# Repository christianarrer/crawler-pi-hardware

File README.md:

# crawler-pi-hardware

Hardware designs for **crawler-pi**, an autonomous tracked robot based on a Raspberry Pi and ROS 2.

This repository contains KiCad PCB projects, manufacturing files, and hardware documentation. Additional 3D-printable customization parts may be included in the future, subject to the necessary permissions.

The ROS 2 software is maintained separately in [crawler-pi](https://github.com/christianarrer/crawler-pi).

## PCB projects

### 1. crawler-pi — Sensor and power distribution board

**Location:** [`pcb/crawler-pi/`](pcb/crawler-pi/)

A distribution and interface PCB for the crawler's Raspberry Pi electronics. Its purpose is to simplify the wiring between the Raspberry Pi, sensors, motor-driver control signals, lighting, and power components.

The board provides:

- Connections for I²C sensors and related peripheral wiring.
- GPIO connections for the left and right motor-driver control signals.
- A GPIO-controlled switch for the headlights.
- Battery and DC/DC buck-converter connections for the crawler's power distribution.
- Reverse-polarity protection and fuse protection.

The project includes KiCad schematic and PCB design files. The [`gerber/`](pcb/crawler-pi/gerber/) directory contains manufacturing outputs from an earlier board revision.

#### Through-hole (THT) components — hand soldering

The following **19 components** require through-hole hand soldering. The reference designators and part numbers are reproduced from the original BOM (including `BS170` and `178.6165.0001`).

| Reference | Manufacturer | MPN | LCSC | Type |
| --- | --- | --- | --- | --- |
| R_POL_PD1 | VISHAY | RN60E1003BRE6 | C1796719 | Resistor |
| R_LED_GATE1 | YAGEO | MFR-25FRF52-100R | C1740087 | Resistor |
| R_LED_PD1 | VISHAY | RN60E1003BRE6 | C1796719 | Resistor |
| Q_PMOS_GDS | onsemi | FQP27P06 | C462764 | p-channel MOSFET |
| BS170 | onsemi | BS170 | C111691 | n-channel MOSFET |
| 178.6165.0001 | Littelfuse | 178.6165.0001 | C207060 | Fuseholder |
| J_BATT1 | CUI | TB010-508-02BE | C5954901 | Terminal Block |
| J_MOT_DRV_L_PWR1 | CUI | TB010-508-02BE | C5954901 | Terminal Block |
| J_MOT_DRV_R_PWR1 | CUI | TB010-508-02BE | C5954901 | Terminal Block |
| J_PWR_SWITCH1 | CUI | TB010-508-02BE | C5954901 | Terminal Block |
| J_POWER_MON_PWR1 | Amphenol | VI0421550000G | C3816565 | Terminal Block |
| J_BUCk1 | Amphenol | VI0421550000G | C3816565 | Terminal Block |
| J_RPI1 | ZHOURI | PC104-2*20 | C5307344 | Pin Stacking Header 2x20 |
| J_PWR_MON_I2C1 | hanxia | HX PH254-01-04-Z-L11.5 | C52016392 | Pin Header 1x4 |
| J_ODO_L_I2C1 | hanxia | HX PH254-01-04-Z-L11.5 | C52016392 | Pin Header 1x4 |
| J_IMU_I2C1 | hanxia | HX PH254-01-04-Z-L11.5 | C52016392 | Pin Header 1x4 |
| J_ODO_R_I2C1 | hanxia | HX PH254-01-04-Z-L11.5 | C52016392 | Pin Header 1x4 |
| J_MOT_DRV_L_CTRL1 | hanxia | HX PZ2.54-2x4P ZZ | C32713277 | Pin Header 2x4 |
| J_MOT_DRV_R_CTRL1 | hanxia | HX PZ2.54-2x4P ZZ | C32713277 | Pin Header 2x4 |

**Documentation still to be added:** connector assignments, assembly instructions, and board-specific wiring notes. Consult the schematic and PCB files for authoritative pin assignments and component values.

### 2. crawler-pi-charger — NiMH charger and power-path board

**Location:** [`pcb/crawler-pi-charger/`](pcb/crawler-pi-charger/)

**Status: Work in progress — not yet validated for construction or operation.**

This project aims to provide an integrated charging and power-path solution for the crawler's **6-cell (7.2 V nominal) NiMH battery pack** and docking station.

The design is based on the **Analog Devices LTC4011** NiMH battery charger controller. The intended functionality includes:

- Charging the NiMH battery when the crawler is connected to its dock.
- Using the LTC4011's supported fast-charge termination and battery-temperature sensing features.
- Providing a power path between the external dock supply, battery, and crawler system load.
- Supporting continued system operation when docking power is connected or removed, subject to the final switching and power-budget design.
- Interfaces for the docking-station supply, battery, system power, and DC/DC converter connections.

The design explores MOSFET-based power-path switching inspired by the Analog Devices DC674B demonstration circuit. Power-path component ratings, charger configuration, thermal protection, current limits, and the distribution of power to the motors and Raspberry Pi must be verified before use.

**Important:** This is an experimental hardware project. Do not assume that the present schematic is suitable for unattended battery charging or direct connection to the robot without electrical verification and testing.

## Repository structure

```text
crawler-pi-hardware/
├── pcb/
│   ├── crawler-pi/          # Sensor, GPIO, and power distribution PCB
│   │   └── gerber/          # Manufacturing files
│   └── crawler-pi-charger/  # NiMH charger and power-path PCB (WIP)
└── stl/                     # Possible future 3D-printable parts
```

The `stl/` directory is **planned**, not necessarily present in the repository. Original designs or adaptations of third-party parts will only be published where redistribution is permitted.

## Working with the designs

Open each PCB project using its `.kicad_pro` file in KiCad. Before ordering or assembling boards, review the schematic, PCB layout, design-rule checks, component footprints, and manufacturing outputs. Existing Gerber files represent a particular exported revision and should not be assumed to match subsequent schematic or PCB edits.

## License

See [LICENSE](LICENSE) for the repository's current license. Rights to any third-party reference designs, components, and future mechanical files remain subject to their respective owners and licenses.

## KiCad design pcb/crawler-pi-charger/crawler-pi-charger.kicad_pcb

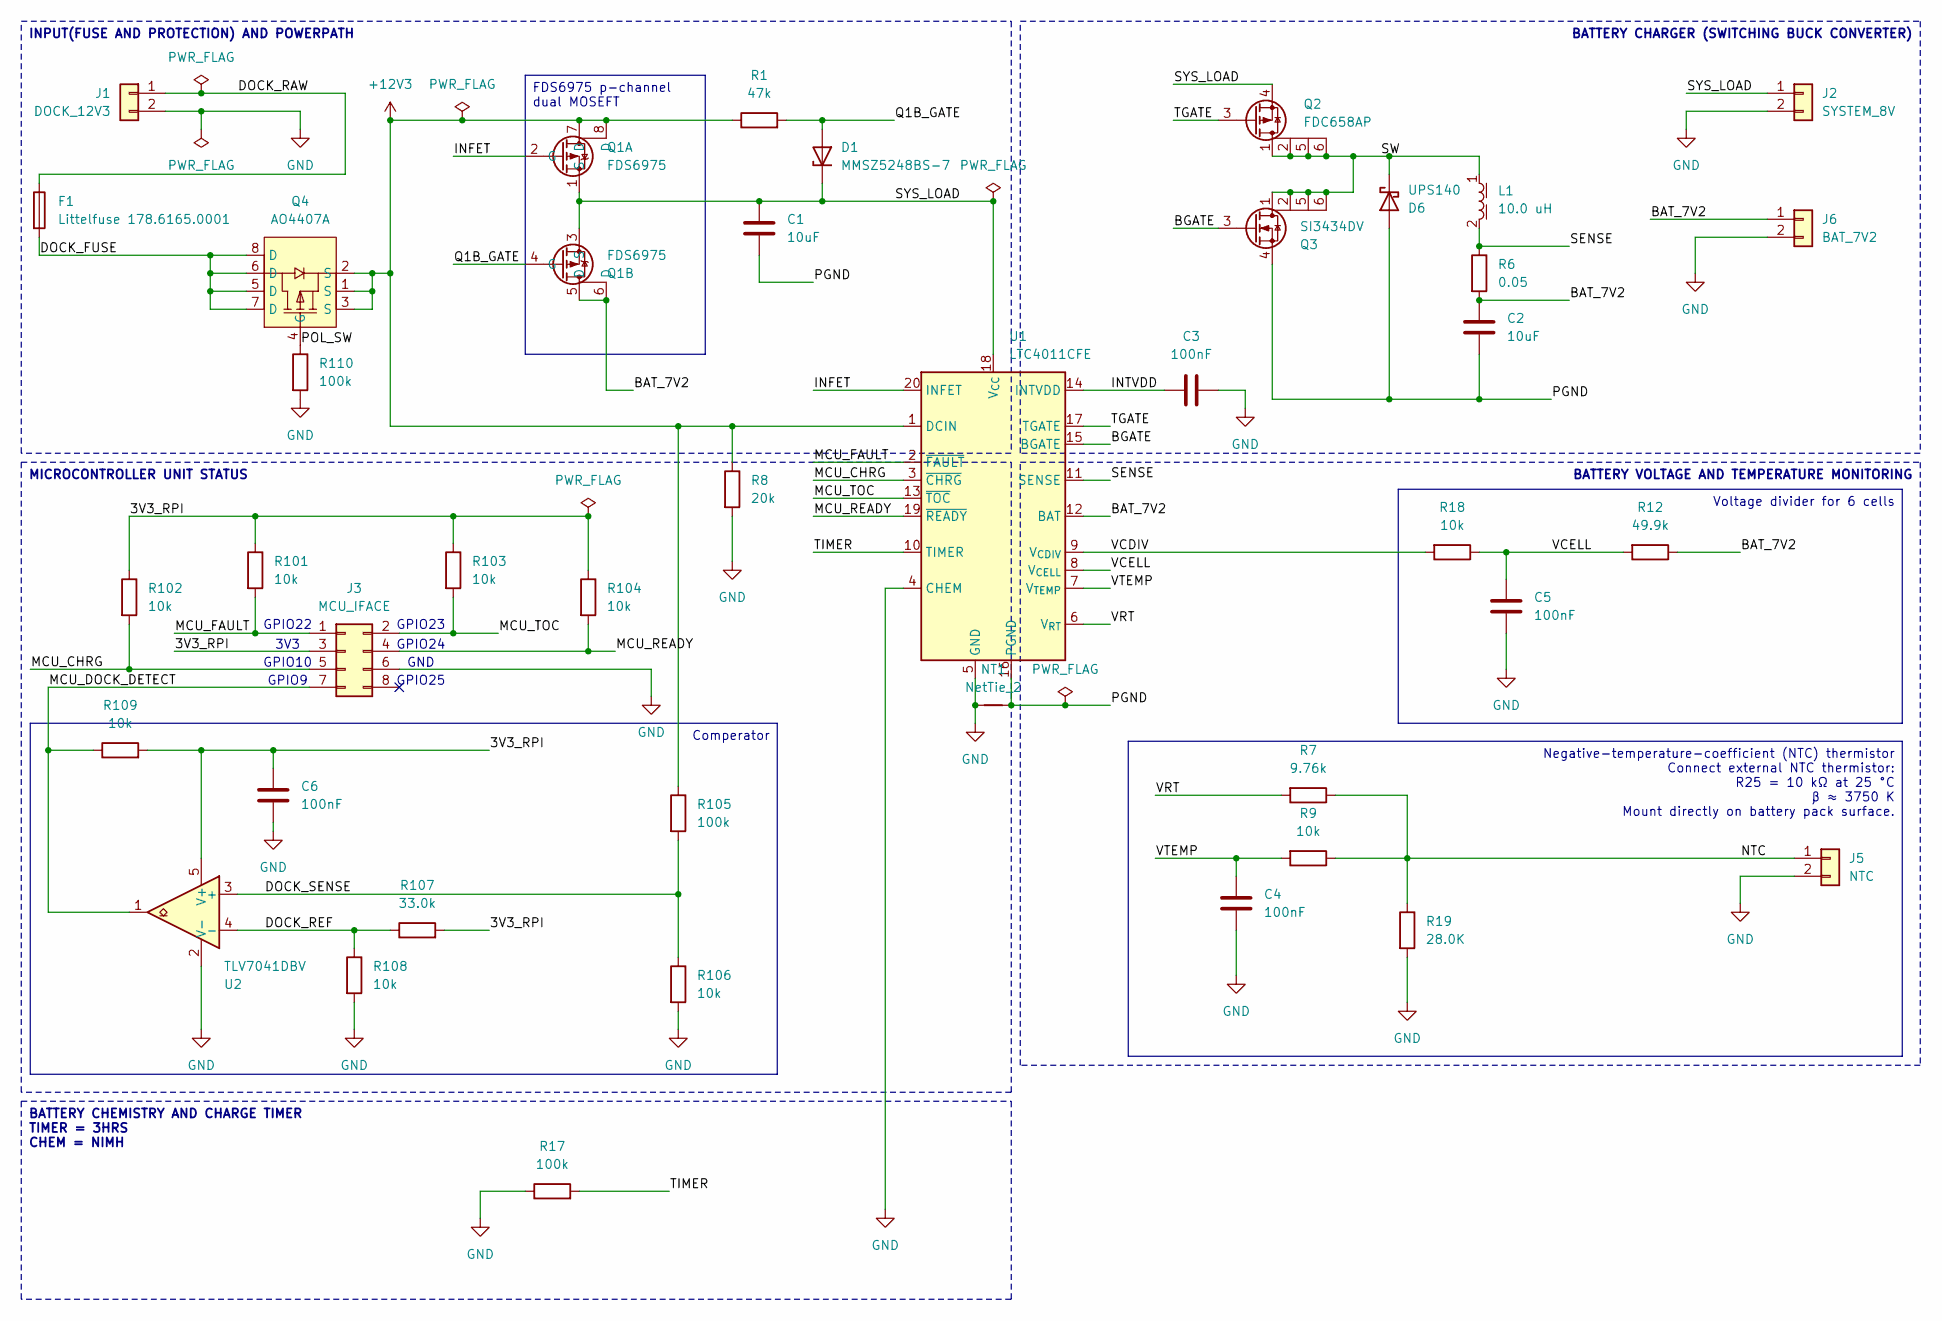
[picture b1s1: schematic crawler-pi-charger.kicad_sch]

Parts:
C1, C2: 10uF; C_1210_3225Metric; MPN TMK325BJ106MM-T; LCSC C92835
C3, C4, C5: 100nF; C_0603_1608Metric; MPN 06033D104KAT2A; LCSC C179462
C6: 100nF; C_0603_1608Metric; MPN CC0603KRX7R9BB104; LCSC C14663
D1: MMSZ5248BS-7; D_SOD-323; MPN MMSZ5248BS-7; LCSC C460919
D6: UPS140; D_Powermite_LargeCathode; MPN UPS140E3/TR7; LCSC C3757274
F1: Littelfuse 178.6165.0001; FuseHolder_Blade_ATO_Littelfuse_FLR_178.6165; MPN 178.6165.0001; LCSC C207060
J1: DOCK_12V3; TerminalBlock_CUI_TB007-508-02_1x02_P5.08mm_Horizontal
J2: SYSTEM_8V; TerminalBlock_CUI_TB007-508-02_1x02_P5.08mm_Horizontal
J3: MCU_IFACE; PinHeader_2x04_P2.54mm_Vertical
J5: NTC; TerminalBlock_CUI_TB007-508-02_1x02_P5.08mm_Horizontal
J6: BAT_7V2; TerminalBlock_CUI_TB007-508-02_1x02_P5.08mm_Horizontal
L1: 10.0 uH; L_Wurth_WE-LHMI-7050; Part Number 74437349100
NT1: NetTie_2; NetTie-2_SMD_Pad0.5mm
Q1: FDS6975; SOIC-8_3.9x4.9mm_P1.27mm; MPN FDS6975; LCSC C903635
Q2: FDC658AP; SuperSOT-6; MPN FDC658AP; LCSC C3280198
Q3: SI3434DV; TSOP-6_1.65x3.05mm_P0.95mm; MPN SI3434DV-T1-E3; LCSC C5456592
Q4: AO4407A; SOIC-8_3.9x4.9mm_P1.27mm; MPN AO4407A; LCSC C16072
R1: 47k; R_0402_1005Metric; MPN CRCW040247K0JNED; LCSC C71619
R6: 0.05; R_1206_3216Metric; MPN ERJ-L08KJ50MV; LCSC C3914720
R7: 9.76k; R_0402_1005Metric; MPN CRCW04029K76FKED; LCSC C843909
R8: 20k; R_0402_1005Metric; MPN CRCW040220K0JNED; LCSC C482264
R9, R18, R101, R102, R103, R104, R106, R108, R109: 10k; R_0402_1005Metric; MPN CRCW040210K0FKED; LCSC C71617
R12: 49.9k; R_0402_1005Metric; MPN CRCW040249K9FKED; LCSC C350874
R17, R105, R110: 100k; R_0402_1005Metric; MPN CRCW0402100KFKED; LCSC C481918
R19: 28.0K; R_0402_1005Metric; MPN CRCW040228K0FKED; LCSC C844308
R107: 33.0k; R_0402_1005Metric; MPN CRCW040233K0FKED; LCSC C482153
U1: LTC4011CFE; HTSSOP-20-1EP_4.4x6.5mm_P0.65mm_EP2.74x3.86mm; MPN LTC4011CFE#TRPBF; LCSC C580822
U2: TLV7041DBV; SOT-23-5; MPN TLV7041DBVR; LCSC C702122

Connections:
+12V3: Q1.7 (D), Q1.8 (D), Q4.1 (S), Q4.2 (S), Q4.3 (S), R1.1, R8.1, R105.1, U1.1 (DCIN)
/3V3_RPI: C6.1, J3.3, R101.1, R102.1, R103.1, R104.1, R107.2, R109.2, U2.5 (V+)
/BAT_7V2: C2.1, J6.1, Q1.5 (D), Q1.6 (D), R6.2, R12.1, U1.12 (BAT)
/BGATE: Q3.3 (G), U1.15 (BGATE)
/DOCK_FUSE: F1.2, Q4.5 (D), Q4.6 (D), Q4.7 (D), Q4.8 (D)
/DOCK_RAW: F1.1, J1.1
/DOCK_REF: R107.1, R108.1, U2.4 (-)
/DOCK_SENSE: R105.2, R106.1, U2.3 (+)
/INFET: Q1.2 (G), U1.20 (INFET)
/INTVDD: C3.1, U1.14 (INTVDD)
/MCU_CHRG: J3.5, R102.2, U1.3 (~CHRG)
/MCU_DOCK_DETECT: J3.7, R109.1, U2.1
/MCU_FAULT: J3.1, R101.2, U1.2 (~FAULT)
/MCU_READY: J3.4, R104.2, U1.19 (~READY)
/MCU_TOC: J3.2, R103.2, U1.13 (~TOC)
/NTC: J5.1, R7.1, R9.1, R19.1
/PGND: C1.2, C2.2, D6.2 (A), NT1.2, Q3.4 (S), U1.16 (PGND)
/POL_SW: Q4.4 (G), R110.1
/Q1B_GATE: D1.2 (A), Q1.4 (G), R1.2
/SENSE: L1.2, R6.1, U1.11 (SENSE)
/SW: D6.1 (K), L1.1, Q2.1 (D), Q2.2 (D), Q2.5 (D), Q2.6 (D), Q3.1 (D), Q3.2 (D), Q3.5 (D), Q3.6 (D)
/SYS_LOAD: C1.1, D1.1 (K), J2.1, Q1.1 (S), Q1.3 (S), Q2.4 (S), U1.18 (V_{CC})
/TGATE: Q2.3 (G), U1.17 (TGATE)
/TIMER: R17.2, U1.10 (TIMER)
/VCDIV: R18.2, U1.9 (V_{CDIV})
/VCELL: C5.1, R12.2, R18.1, U1.8 (V_{CELL})
/VRT: R7.2, U1.6 (V_{RT})
/VTEMP: C4.1, R9.2, U1.7 (V_{TEMP})
GND: C3.2, C4.2, C5.2, C6.2, J1.2, J2.2, J3.6, J5.2, J6.2, NT1.1, R8.2, R17.1, R19.2, R106.2, R108.2, R110.2, U1.4 (CHEM), U1.5 (GND), U1.21 (GND), U2.2 (V-)

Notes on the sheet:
GPIO24
GPIO9
GPIO22
GND
GPIO25
GPIO10
3V3
GPIO23
Negative-temperature-coefficient (NTC) thermistor Connect external NTC thermistor: R25 = 10 kΩ at 25 °C β ≈ 3750 K Mount directly on battery pack surface.
BATTERY CHARGER (SWITCHING BUCK CONVERTER)
Comperator
BATTERY VOLTAGE AND TEMPERATURE MONITORING
BATTERY CHEMISTRY AND CHARGE TIMER TIMER = 3HRS CHEM = NIMH
INPUT(FUSE AND PROTECTION) AND POWERPATH
MICROCONTROLLER UNIT STATUS
Voltage divider for 6 cells
FDS6975 p-channel dual MOSEFT

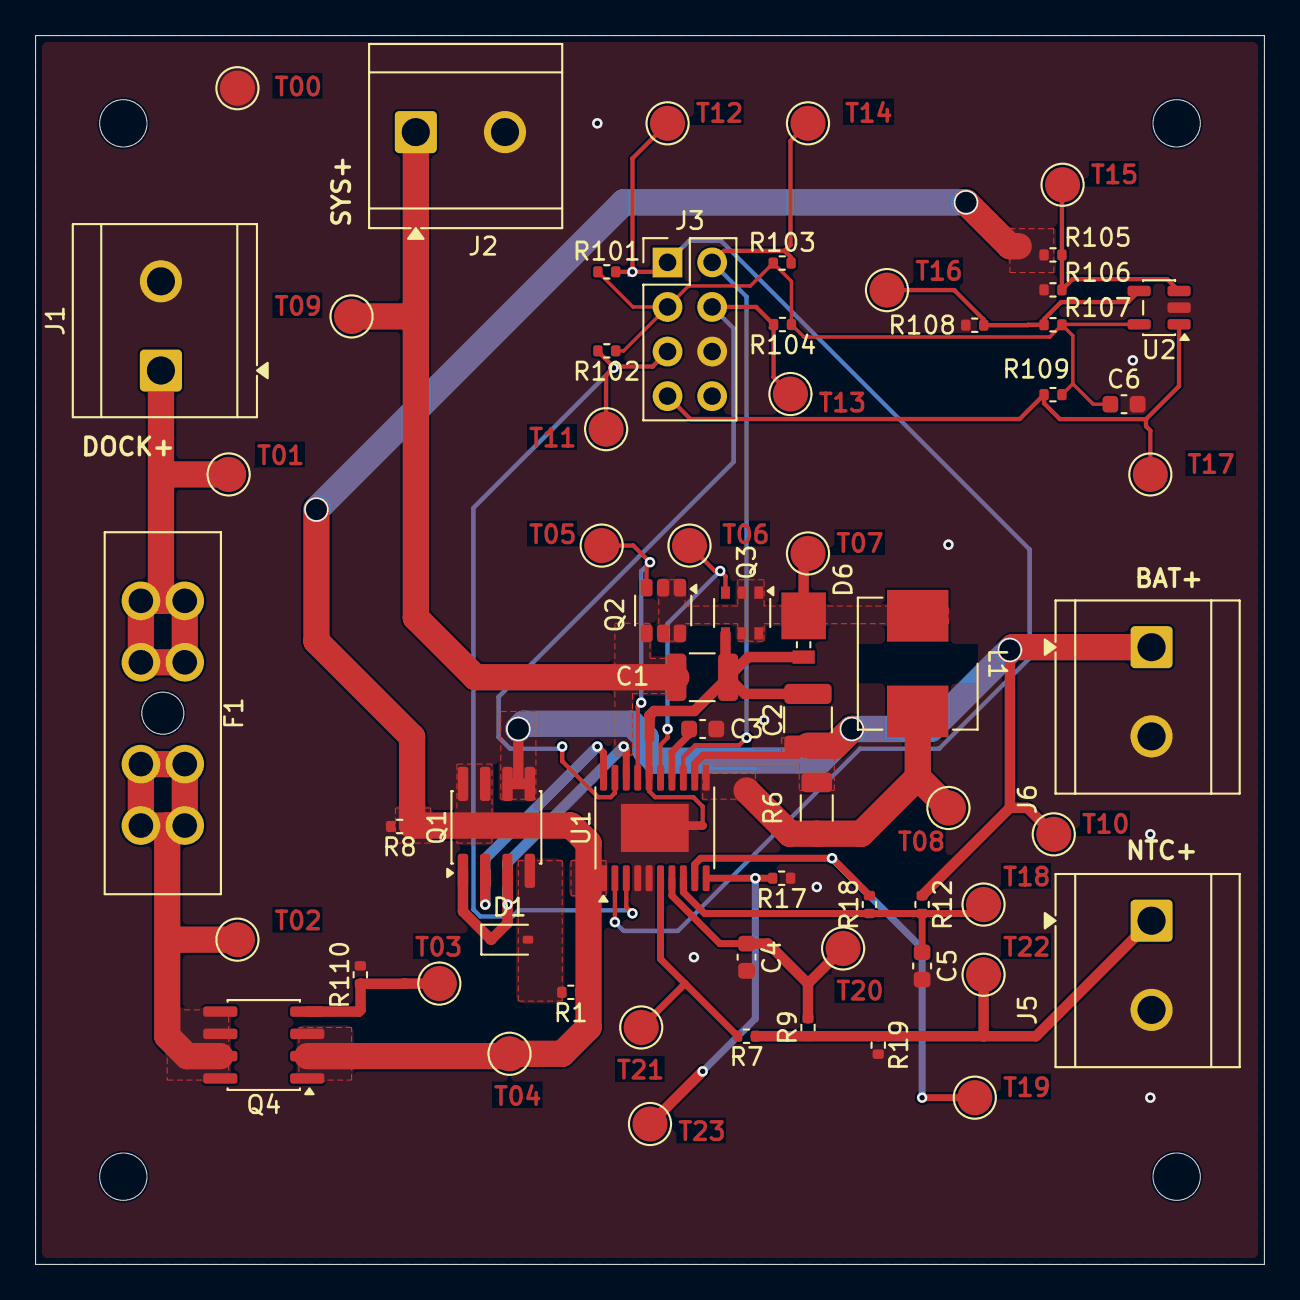
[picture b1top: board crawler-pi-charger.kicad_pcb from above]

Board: 2 copper layers, 70.0 x 70.0 mm, 41 parts (0 on the bottom side), 29 nets.

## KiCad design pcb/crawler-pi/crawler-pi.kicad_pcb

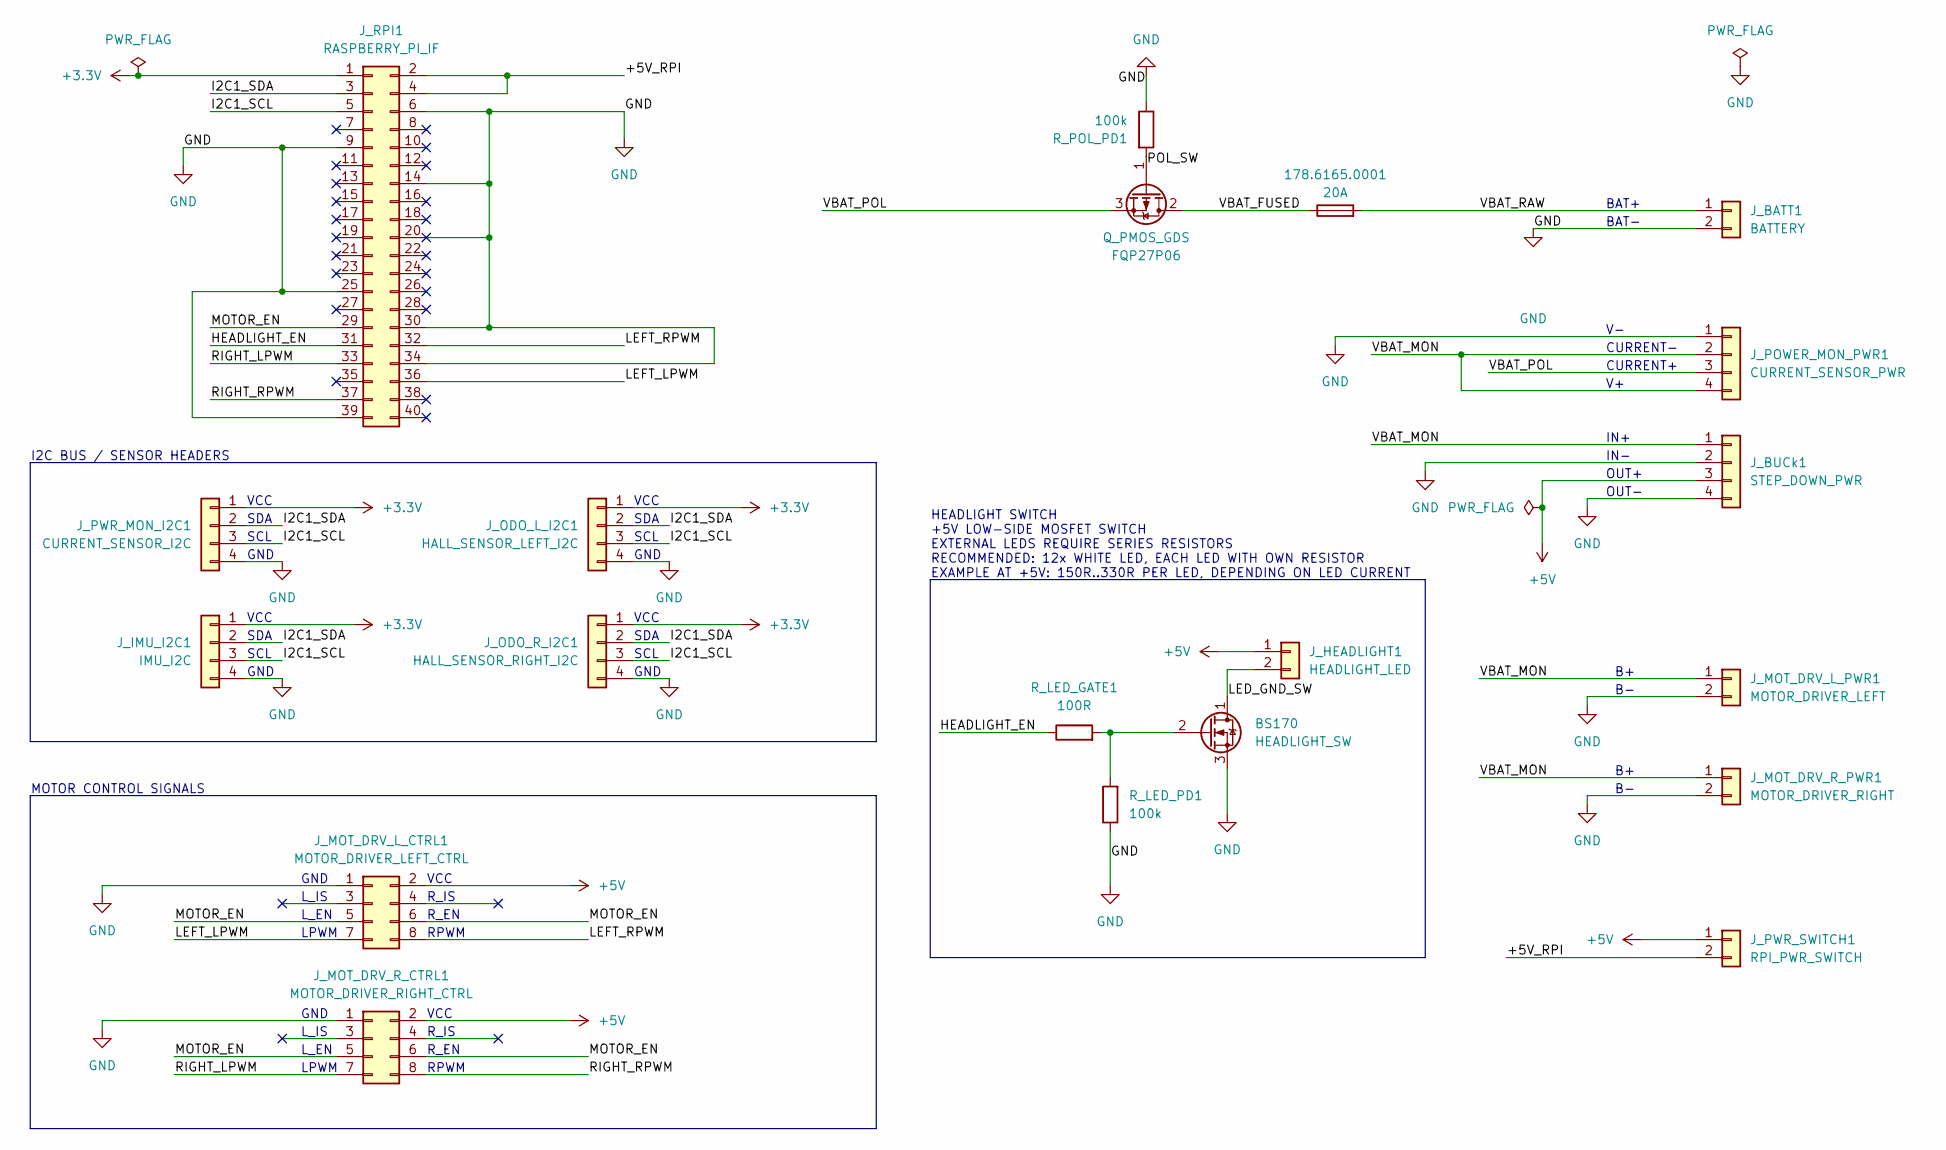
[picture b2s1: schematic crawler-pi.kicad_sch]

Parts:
178.6165.0001: 20A; FuseHolder_Blade_ATO_Littelfuse_FLR_178.6165
BS170: HEADLIGHT_SW; TO-92_Inline
FQP27P06: Q_PMOS_GDS; TO-220-3_Horizontal_TabDown
J_BATT1: BATTERY; TerminalBlock_bornier-2_P5.08mm
J_BUCk1: STEP_DOWN_PWR; TerminalBlock_bornier-4_P5.08mm
J_HEADLIGHT1: HEADLIGHT_LED; TerminalBlock_bornier-2_P5.08mm
J_IMU_I2C1: IMU_I2C; PinHeader_1x04_P2.54mm_Vertical
J_MOT_DRV_L_CTRL1: MOTOR_DRIVER_LEFT_CTRL; PinHeader_2x04_P2.54mm_Vertical
J_MOT_DRV_L_PWR1: MOTOR_DRIVER_LEFT; TerminalBlock_bornier-2_P5.08mm
J_MOT_DRV_R_CTRL1: MOTOR_DRIVER_RIGHT_CTRL; PinHeader_2x04_P2.54mm_Vertical
J_MOT_DRV_R_PWR1: MOTOR_DRIVER_RIGHT; TerminalBlock_bornier-2_P5.08mm
J_ODO_L_I2C1: HALL_SENSOR_LEFT_I2C; PinHeader_1x04_P2.54mm_Vertical
J_ODO_R_I2C1: HALL_SENSOR_RIGHT_I2C; PinHeader_1x04_P2.54mm_Vertical
J_POWER_MON_PWR1: CURRENT_SENSOR_PWR; TerminalBlock_bornier-4_P5.08mm
J_PWR_MON_I2C1: CURRENT_SENSOR_I2C; PinHeader_1x04_P2.54mm_Vertical
J_PWR_SWITCH1: RPI_PWR_SWITCH; TerminalBlock_bornier-2_P5.08mm
J_RPI1: RASPBERRY_PI_IF; PinHeader_2x20_P2.54mm_Vertical
R_LED_GATE1: 100R; R_Axial_DIN0207_L6.3mm_D2.5mm_P7.62mm_Horizontal
R_LED_PD1: 100k; R_Axial_DIN0207_L6.3mm_D2.5mm_P7.62mm_Horizontal
R_POL_PD1: 100k; R_Axial_DIN0207_L6.3mm_D2.5mm_P7.62mm_Horizontal

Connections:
+3.3V: J_IMU_I2C1.1, J_ODO_L_I2C1.1, J_ODO_R_I2C1.1, J_PWR_MON_I2C1.1, J_RPI1.1
+5V: J_BUCk1.3, J_HEADLIGHT1.1, J_MOT_DRV_L_CTRL1.2, J_MOT_DRV_R_CTRL1.2, J_PWR_SWITCH1.1
/+5V_RPI: J_PWR_SWITCH1.2, J_RPI1.2, J_RPI1.4
/HEADLIGHT_EN: J_RPI1.31, R_LED_GATE1.1
/I2C1_SCL: J_IMU_I2C1.3, J_ODO_L_I2C1.3, J_ODO_R_I2C1.3, J_PWR_MON_I2C1.3, J_RPI1.5
/I2C1_SDA: J_IMU_I2C1.2, J_ODO_L_I2C1.2, J_ODO_R_I2C1.2, J_PWR_MON_I2C1.2, J_RPI1.3
/LED_GND_SW: BS170.1 (D), J_HEADLIGHT1.2
/LEFT_LPWM: J_MOT_DRV_L_CTRL1.7, J_RPI1.36
/LEFT_RPWM: J_MOT_DRV_L_CTRL1.8, J_RPI1.32
/MOTOR_EN: J_MOT_DRV_L_CTRL1.5, J_MOT_DRV_L_CTRL1.6, J_MOT_DRV_R_CTRL1.5, J_MOT_DRV_R_CTRL1.6, J_RPI1.29; also elsewhere on the board
/RIGHT_LPWM: J_MOT_DRV_R_CTRL1.7, J_RPI1.33
/RIGHT_RPWM: J_MOT_DRV_R_CTRL1.8, J_RPI1.37
/VBAT_FUSED: 178.6165.0001.1, FQP27P06.2 (D)
/VBAT_MON: J_BUCk1.1, J_MOT_DRV_L_PWR1.1, J_MOT_DRV_R_PWR1.1, J_POWER_MON_PWR1.2, J_POWER_MON_PWR1.4
/VBAT_POL: FQP27P06.3 (S), J_POWER_MON_PWR1.3
/VBAT_RAW: 178.6165.0001.2, J_BATT1.1
GND: BS170.3 (S), J_BATT1.2, J_BUCk1.2, J_BUCk1.4, J_IMU_I2C1.4, J_MOT_DRV_L_CTRL1.1, J_MOT_DRV_L_PWR1.2, J_MOT_DRV_R_CTRL1.1, J_MOT_DRV_R_PWR1.2, J_ODO_L_I2C1.4, J_ODO_R_I2C1.4, J_POWER_MON_PWR1.1, J_PWR_MON_I2C1.4, J_RPI1.6, J_RPI1.9, J_RPI1.14, J_RPI1.20, J_RPI1.25, J_RPI1.30, J_RPI1.34, J_RPI1.39, R_LED_PD1.1, R_POL_PD1.1; also elsewhere on the board
unnamed: BS170.2 (G), R_LED_GATE1.2, R_LED_PD1.2
unnamed: FQP27P06.1 (G), R_POL_PD1.2

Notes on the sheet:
VCC
RPWM
R_IS
CURRENT-
SDA
GND
CURRENT+
SCL
L_EN
MOTOR CONTROL SIGNALS
R_EN
L_IS
LPWM
HEADLIGHT SWITCH +5V LOW-SIDE MOSFET SWITCH EXTERNAL LEDS REQUIRE SERIES RESISTORS RECOMMENDED: 12x WHITE LED, EACH LED WITH OWN RESISTOR EXAMPLE AT +5V: 150R..330R PER LED, DEPENDING ON LED CURRENT
IN-
OUT-
BAT-
OUT+
BAT+
IN+
I2C BUS / SENSOR HEADERS

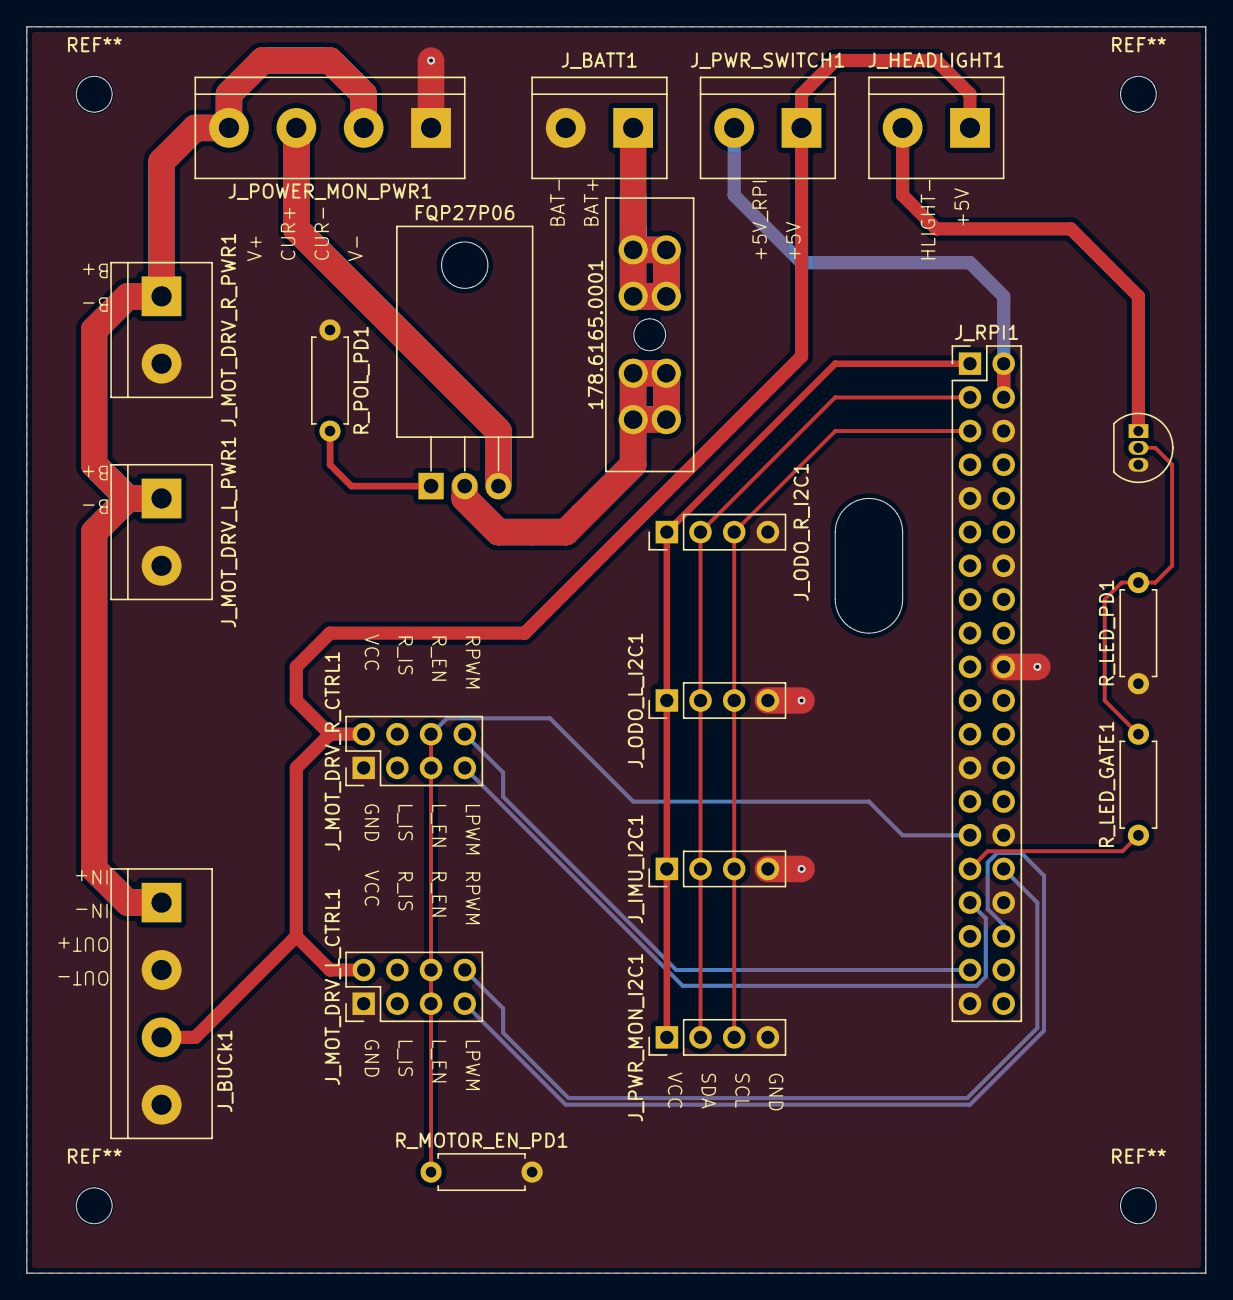
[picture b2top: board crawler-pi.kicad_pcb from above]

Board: 2 copper layers, 88.9 x 94.0 mm, 21 parts (0 on the bottom side), 19 nets.

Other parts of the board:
R_MOTOR_EN_PD1: 10k; R_Axial_DIN0207_L6.3mm_D2.5mm_P7.62mm_Horizontal

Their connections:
/MOTOR_EN: R_MOTOR_EN_PD1.1; also elsewhere on the board
GND: R_MOTOR_EN_PD1.2; also elsewhere on the board
